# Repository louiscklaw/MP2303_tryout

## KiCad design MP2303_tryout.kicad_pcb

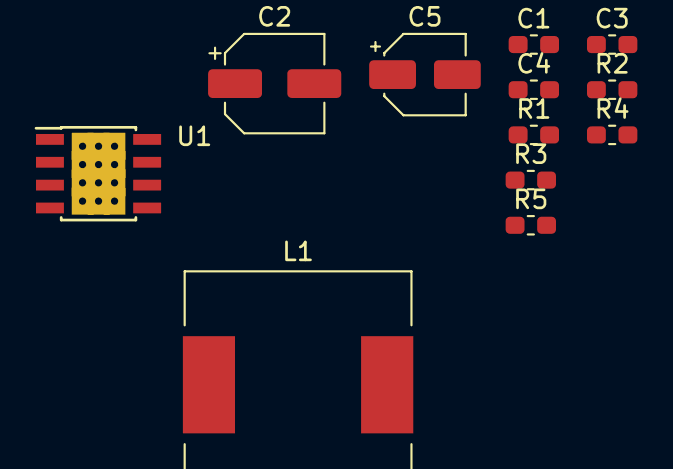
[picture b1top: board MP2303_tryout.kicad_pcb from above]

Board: 2 copper layers, 12 parts (0 on the bottom side), 10 nets, no tracks yet.

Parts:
C1: C103,0603; C_0603_1608Metric_Pad1.05x0.95mm_HandSolder
C2: CP10uf,50V; CP_Elec_5x5.3
C3: C104,0603; C_0603_1608Metric_Pad1.05x0.95mm_HandSolder
C4: C472,0603; C_0603_1608Metric_Pad1.05x0.95mm_HandSolder
C5: CP47uf,10V; CP_Elec_4x5.3
L1: L_10uH_shielded,CD127; L_CD127_shielded
R1: R104,0603; R_0603_1608Metric_Pad1.05x0.95mm_HandSolder
R2: R303,0603; R_0603_1608Metric_Pad1.05x0.95mm_HandSolder
R3: R473,0603; R_0603_1608Metric_Pad1.05x0.95mm_HandSolder
R4: R103,0603; R_0603_1608Metric_Pad1.05x0.95mm_HandSolder
R5: R432,0603; R_0603_1608Metric_Pad1.05x0.95mm_HandSolder
U1: MP2303A_ALT; MP2303,SOIC-8_3.9x4.9mm_P1.27mm,thermal_via

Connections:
GND: C2.2, C3.2, C5.2, R3.2, R4.2, R5.2, U1.4
unnamed: C1.1, L1.1, U1.3
unnamed: C1.2, U1.1
unnamed: C3.1, U1.8
unnamed: C4.1, U1.6
unnamed: C4.2, R5.1
unnamed: C5.1, L1.2, R2.1
unnamed: R1.1, U1.2
unnamed: R1.2, R3.1, U1.7
unnamed: R2.2, R4.1, U1.5

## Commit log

2019-05-07 update,
2019-05-08 update to remove backup files,
2020-05-06 ci: init travis build config,
2020-05-06 ci: init travis token,
